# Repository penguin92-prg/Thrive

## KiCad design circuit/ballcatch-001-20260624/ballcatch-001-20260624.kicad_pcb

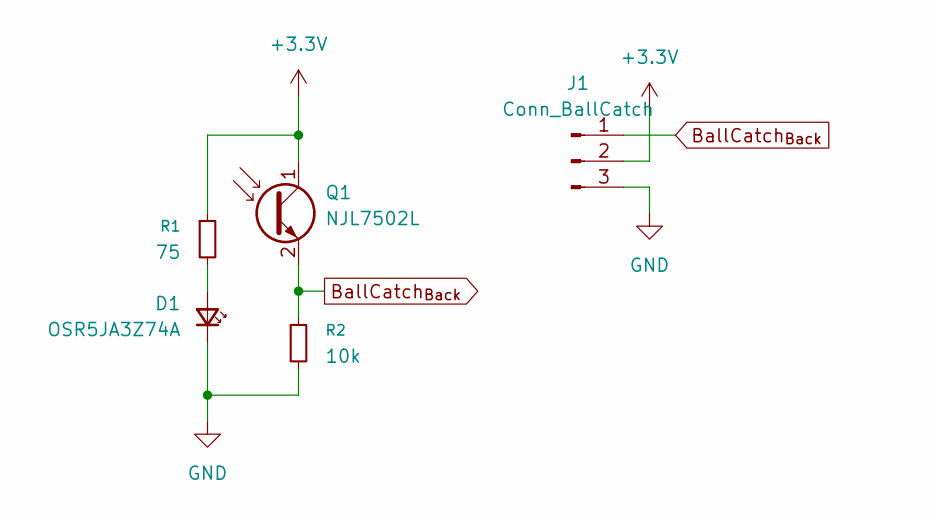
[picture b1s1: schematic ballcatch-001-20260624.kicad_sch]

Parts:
D1: OSR5JA3Z74A; LED_D3.0mm
J1: Conn_BallCatch; PinHeader_1x03_P2.54mm_Vertical
Q1: NJL7502L
R1: 75; R_Axial_DIN0207_L6.3mm_D2.5mm_P7.62mm_Horizontal
R2: 10k; R_Axial_DIN0207_L6.3mm_D2.5mm_P7.62mm_Horizontal

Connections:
+3.3V: J1.2, Q1.1 (C), R1.1
BallCatch_{Back}: J1.1, Q1.2 (E), R2.1
GND: D1.2 (K), J1.3, R2.2
unnamed: D1.1 (A), R1.2

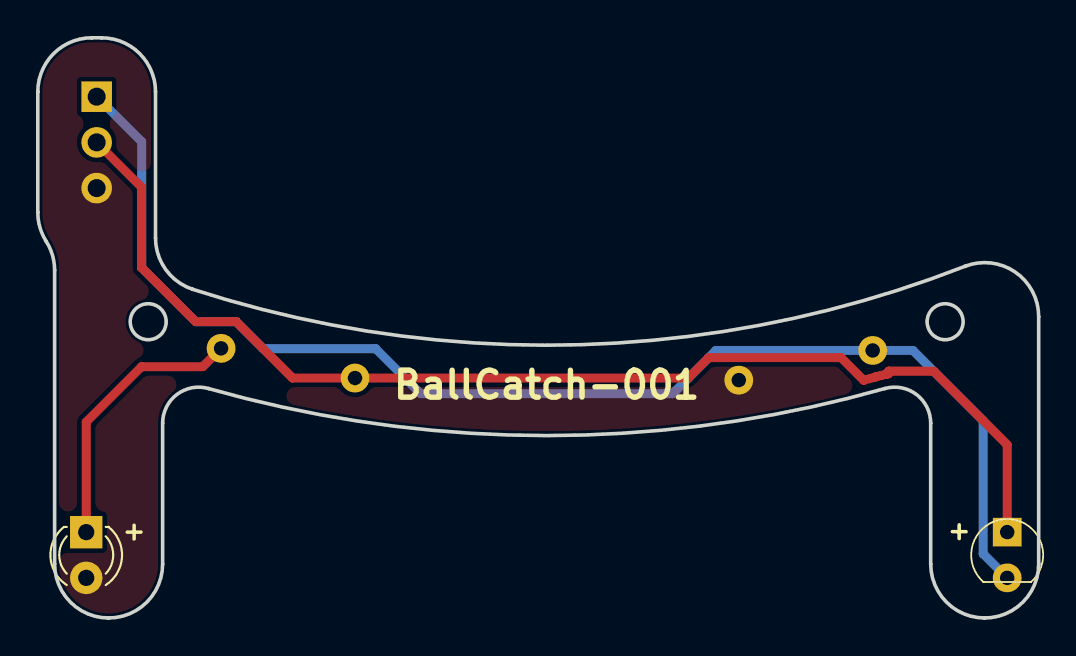
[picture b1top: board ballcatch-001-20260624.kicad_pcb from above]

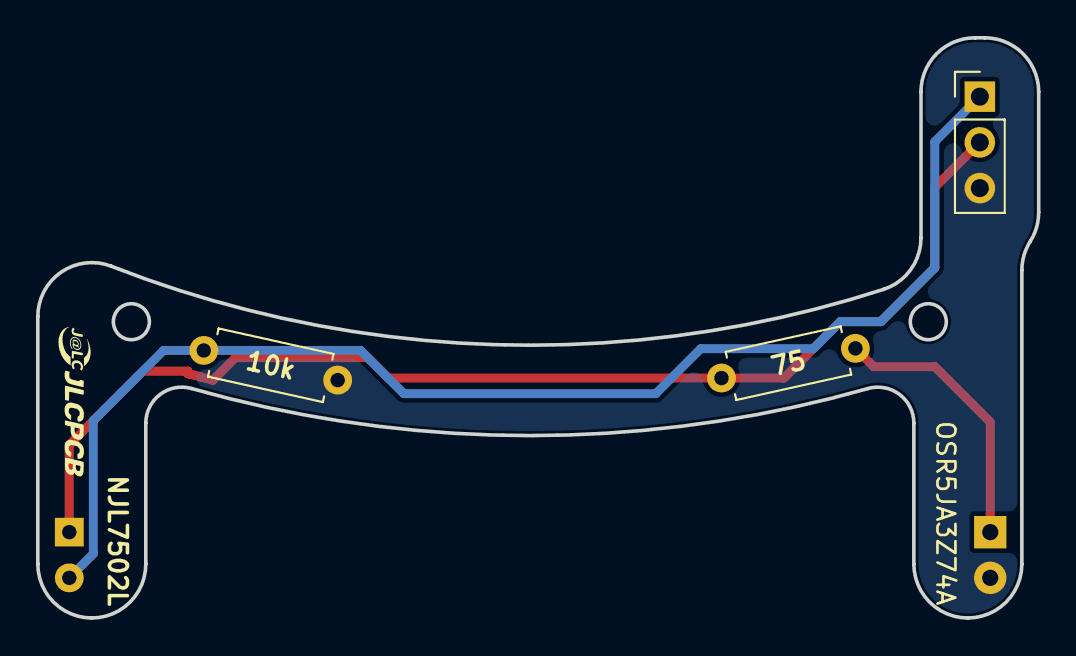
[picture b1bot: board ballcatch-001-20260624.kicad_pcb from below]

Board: 2 copper layers, 55.6 x 32.2 mm, 5 parts (3 on the bottom side), 4 nets.
